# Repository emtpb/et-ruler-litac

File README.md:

# Light to Audio Converter (LitAC)

Did you ever look at an electrical candle and thought to yourself: "Mhmm, I really wonder what the flickering would sound like if I could hear light"?
With this project you will no longer be in the dark!

A photoresistive diode picks up the flickering of your candle and converts it into an electrical signal. The signal then gets amplified (by an OP07) so you can hear it with your headphones or speakers.
You can connect two "LitAC" to have them powered from the same battery, so you only need two batteries for your candle powered orchestra.

# Schematic

# Interactive BOM
An interactive html BOM page with pcb layout and material placement can be found [here](https://emtpb.github.io/et-ruler-litac/bom/ibom.html).

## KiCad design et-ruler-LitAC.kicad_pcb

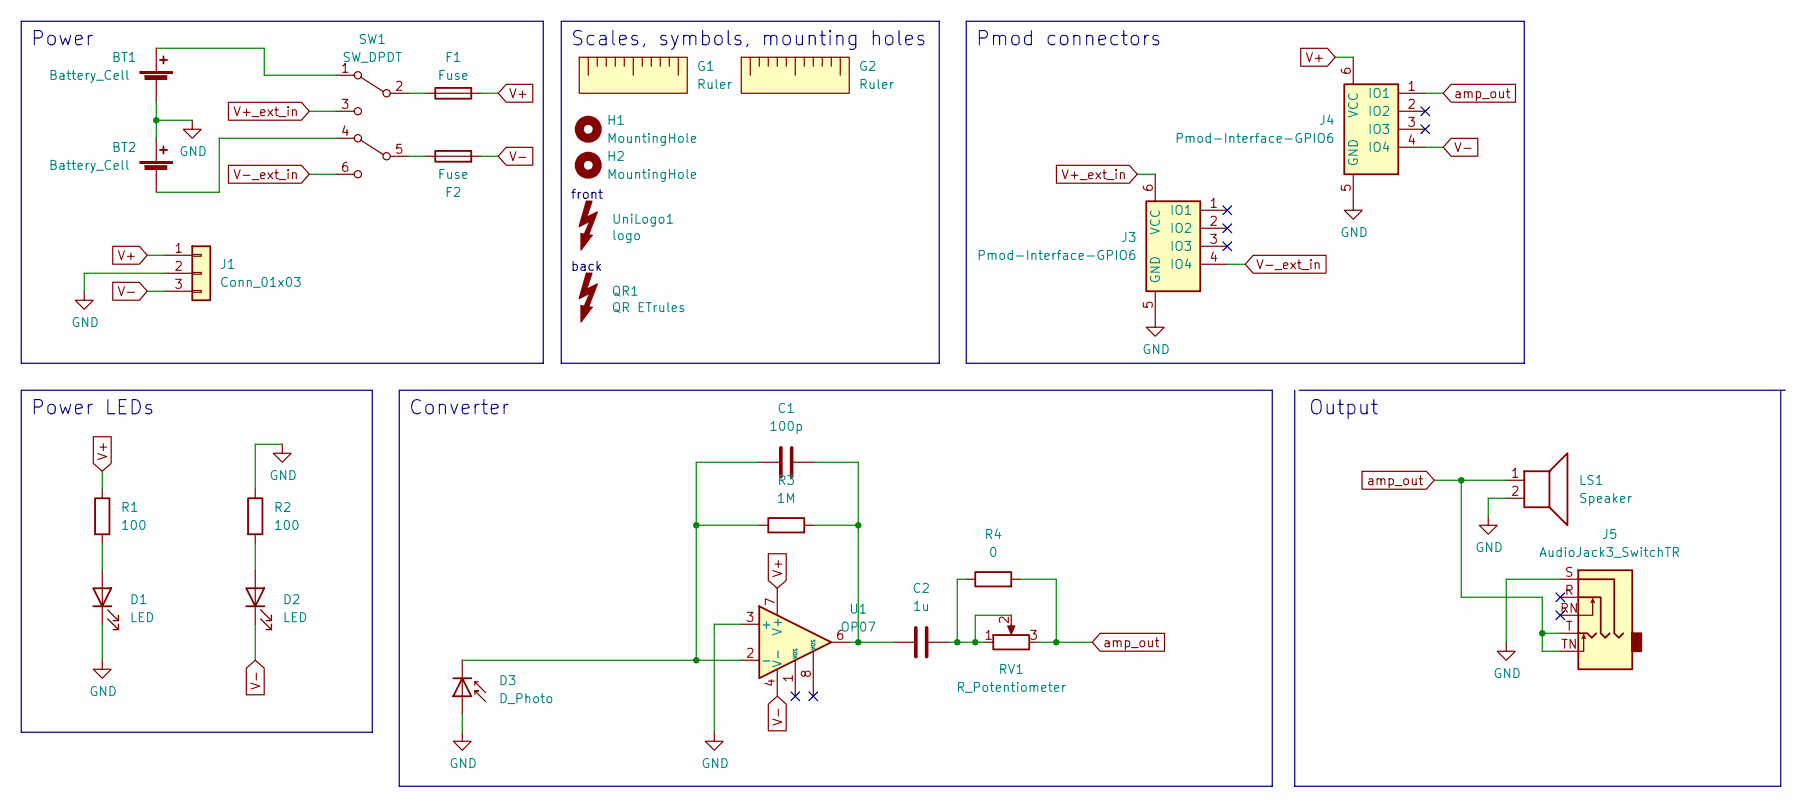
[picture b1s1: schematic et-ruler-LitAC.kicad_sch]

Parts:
BT1, BT2: Battery_Cell; BatteryHolder_Keystone_1060_1x2032_adhesive_Hybrid
C1: 100p; C_0805_THT_5.08mm_Hybrid
C2: 1u; C_0805_THT_5.08mm_Hybrid
D1, D2: LED; LED_THT_SMD_Hybrid_D3.0mm
D3: D_Photo; LED_THT_SMD_Hybrid_D5.0mm
F1, F2: Fuse; R_0805_THT_5.08mm_Hybrid
G1, G2: Ruler; Metric_Ruler_160mm_top
H1, H2: MountingHole; MountingHole_3.2mm_M3
J1: Conn_01x03; PinSocket_1x03_P2.54mm_Vertical
J3: Pmod-Interface-GPIO6; Pmod_Interface_Male6
J4: Pmod-Interface-GPIO6; Pmod_Interface_Female6
J5: AudioJack3_SwitchTR; Jack_3.5mm_Ledino_KB3SPRS_Horizontal
LS1: Speaker; PinSocket_1x02_P2.54mm_Horizontal
QR1: QR ETrules; qr-studiere-et_15x16
R1, R2: 100; R_0805_THT_10.16mm_Hybrid
R3: 1M; R_0805_THT_10.16mm_Hybrid
R4: 0; R_0805_THT_10.16mm_Hybrid
RV1: R_Potentiometer; Potentiometer_ACP_CA14V-15_Vertical
SW1: SW_DPDT; Switch_DPDT_SMD_THT_Hybrid_P2.54
U1: OP07; DIP_SMDIP-8_W7.62mm_Socket
UniLogo1: logo; UPB-Logo_De_15.9X5.6mm

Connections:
GND: BT1.2 (-), BT2.1 (+), D1.1 (K), D3.2 (A), J1.2, J3.5 (GND), J4.5 (GND), J5.S, LS1.2, R2.1, U1.3 (+)
unnamed: BT1.1 (+), SW1.1 (A)
unnamed: BT2.2 (-), SW1.4 (D)
unnamed: C1.2, C2.1, R3.2, U1.6
unnamed: C2.2, R4.1, RV1.1, RV1.2
unnamed: D1.2 (A), R1.2
unnamed: D2.2 (A), R2.2
unnamed: C1.1, D3.1 (K), R3.1, U1.2 (-)
unnamed: F1.1, SW1.2 (B)
unnamed: F2.1, SW1.5 (E)
V+: F1.2, J1.1, J4.6 (VCC), R1.1, U1.7 (V+)
V+_ext_in: J3.6 (VCC), SW1.3 (C)
V-: D2.1 (K), F2.2, J1.3, J4.4 (IO4), U1.4 (V-)
V-_ext_in: J3.4 (IO4), SW1.6 (F)
amp_out: J4.1 (IO1), J5.T, J5.TN, LS1.1, R4.2, RV1.3

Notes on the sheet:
front
Power LEDs
back
Power
Pmod connectors
Output
Converter
Scales, symbols, mounting holes

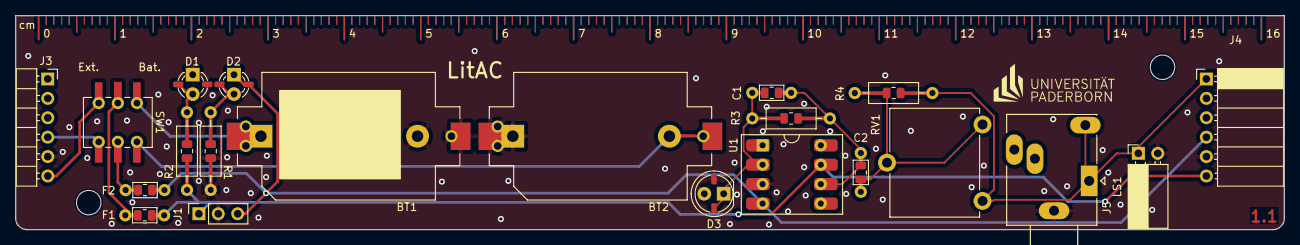
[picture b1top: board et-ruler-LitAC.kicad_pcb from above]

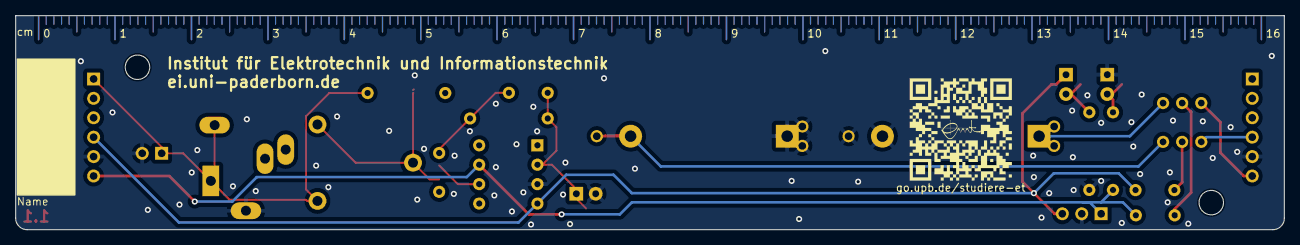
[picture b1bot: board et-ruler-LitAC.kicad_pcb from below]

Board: 2 copper layers, 166.0 x 28.0 mm, 27 parts (2 on the bottom side), 15 nets.

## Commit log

2023-10-30 Add basic schematic from template
2023-10-30 Rename project
2023-10-31 Add Converter schematic
2023-10-31 Fix GND symbol and schematic labels
2023-11-02 Add volume control and headphone jack
2023-11-02 Add PCB from template
2023-11-07 Add correct switch symbol and footprint
2023-11-07 Fix DPDT switch footprint
2023-11-10 Add several footprints
2023-11-10 Add audio jack, links to parts, more footprints
2023-11-13 Exclude scales, holes, and logos from BOM
2024-11-29 Connect amplified signal to pmod
2024-11-29 Convert files to KiCad 7.0 format
2024-11-29 Widen power tracks
2024-11-29 Add parts list
2024-11-29 Add text, labels, and version number
2024-11-29 Only connect tip/left channel of audio jack
2024-11-29 Use correct audio jack
2024-11-29 Use pmod footprints from correct library
2024-11-29 Fix margin around switch
2024-11-29 Add schematic to README
2024-11-29 Fix resistor values
2024-11-29 Use picture without cursor
2024-11-29 Bump to version 1.1
2024-11-29 Fix pitch for SW1 footprint
2024-11-29 Change potentiometer, add axis
2024-11-29 Add text
2024-11-29 Move 'cm' label on backside
2024-11-29 Convert to KiCad 8 format
2024-11-29 Fix via placed on pad
2024-11-29 Fix gnd vias
2024-11-29 Clean up schematic
2024-11-29 Fix ERC warnings
2024-11-29 Fix ERC error related to pins not declared as power pins
2024-11-29 Add interactive BOM
2024-11-29 Dont call the connectors 'Pmod'
2024-11-29 Add title, revision, date and company to schematic
2024-11-29 Add rendering and update picture of schematic
2024-11-29 Add text and images to README
2024-11-29 Add link to ibom in README
2025-05-22 Add interactive BOM link
2025-05-23 Remove old link
